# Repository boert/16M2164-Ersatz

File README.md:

# Ersatz für Hybridschaltkreis 16M2164

Der 16M2164 von KWH (Keramische Werke Hermsdorf) ist ein Speicherschaltkreis in Hybridbauweise.
Er ist vermutlich nur in sehr geringen Stückzahlen hergestellt worden.
Der Hybridschaltkreis enthält 16 mal das Die (ein Stück vom Halbleiterwafer) des Schaltkreises U2164 sowie einige Stützkondensatoren auf einem Keramiksubstrat.  
Der U2164 ist ein dynamischer RAM mit 64kBit.
In Summe enthält der 16M2164 ein MegaBit bzw. 128 kByte Speicher.

Zum Einsatz kommt der Schaltkreis 16M2164 im Speichermodul M036 für den KC85 aus Mühlhausen [^1].  
Um die unbestückten Leiterplatte, die für dieses Modul im Umlauf sind, nutzen zu können, benötigt man i.d.R. einen Ersatz für den 16M2164.

Von U. Zander stammt die urspüngliche Idee einer Schaltkreisersatzplatine, die nur mit vier dRAM-Schaltkreisen auskommt [^2].
Diese Lösung funktioniert leider nicht perfekt.

> [!Note]
> ### dynamischer Speicher
> Bei dynamischen Speichern wird die Information als Ladung in Kondensatoren abgebildet. Durch Leckströme verliert sich diese Ladung mit der Zeit und muß daher regelmäßig aufgefrischt werden (Refresh). Dies geschiet u.a. beim Aktivieren des /RAS-Signals. Der Hersteller gibt dabei an, in welchem Zeitraum jede ROW-Adresse einmal aktiviert werden muß. Normalerweise wird die angelegte ROW-Adresse vom Speichercontroller entsprechend hochgezählt. Bei einem geschickt adressierten Bildwiederholspeicher könnte man auf den Refresh verzichten, da dort durch regelmäßige Lesezugriffe die Information beim Lesen aufgefrischt wird.

In der folgenden Tabelle sind die Refreshzyklen eingier dRAM-Hersteller aufgeführt:

Hersteller  | Speicher-IC | Speichergröße | Refreshzyklen | Refreshzeit | Gehäuse
----------  | ----------- | ------------: | ------------: | ----------: | -------
&nbsp;      | &nbsp;      | _x1 Bit dRAMs_ 
Mostek      | MK4096      |   4k x 1      |   64          |  2 ms       | DIP16
Mostek      | MK4116      |  16k x 1      |  128          |  2 ms       | DIP16
NEC         | µPD4164     |  64k x 1      |  128          |  2 ms       | DIP16
Mostek      | MK4564      |  64k x 1      |  128          |  2 ms       | DIP16, PLCC18
Mostek      | MK4164      |  64k x 1      |  128          |  2 ms       | DIP16
National    | NMC4164     |  64k x 1      |  256          |  4 ms       | DIP16
Siemens     | HYB4164     |  64k x 1      |  256          |  4 ms       | DIP16
Mostek      | MK41256     | 256k x 1      |  256          |  4 ms       | DIP16, PLCC18
Siemens     | HYB51100    |   1M x 1      |  512          |  8 ms       | SOJ26
&nbsp;      | &nbsp;      | _x4 Bit dRAMs_ 
TI          | TMS4416     |  16k x 4      |  256          |  4 ms       | DIP18, PLCC18
TI          | SMJ4464     |  64k x 4      |  256          |  4 ms       | DIP18, PLCC18
NEC         | µPD41464    |  64k x 4      |  256          |  4 ms       | DIP18, PLCC18
TI          | SMJ4464     |  64k x 4      |  256          |  4 ms       | DIP18, PLCC18
Mitsubishi  | M5M4464A    |  64k x 4      |  256          |  4 ms       | DIP18, PLCC18, ZIP20
Samsung     | KM41464A    |  64k x 4      |  256          |  4 ms       | DIP18, PLCC18, ZIP20
Siemens     | HYB514256   | 256k x 4      |  512          |  8 ms       | DIP20, SOJ26/20
NEC         | µPD424400   |   1M x 4      | 1024          | 16 ms       | TSOP26, SOJ26/20

Eine Vergleichstabelle von 64k-Bit dRAM-Chips findet sich unter [^7].

Die verwendeten Speicher-IC der Größe 64k x 4 Bit benötigen alle 256 Refreshzyklen. Damit muß der Zähler für den Refresh mindestens acht Bit breit sein.
Die U880/Z80-CPU enthält nur einen 7 Bit-Refreshzähler, der für die Bausteine mit 64 oder 128 Refreshzyklen ausreichend ist.
Die obere Hälfte des Speichers erhält keinen definierten Refresh und verliert mit der Zeit ihren Inhalt.

Im Folgenden sind drei Wege aufgezeigt, um den fehlenden Speicher zu ersetzen: Variante R, Variante D und Variante S.

## Variante R: Refresh
Der übliche Weg ist es, den Refreshzähler zu erweitern.  
Ein Schaltung dafür findet sich z.B. in [^3].

Auch im Grundgerät D001 (KC85/4) werden aus den Signalen /rfsh, mreq und ab6 die Signale RF7 und RF8 gebildet, die den Refreshzähler des Z80 auf 9 Bit erweitern:

Der erweiterte Refreshzähler steht leider nur den interne RAM-Bausteinen auf der Hauptplatine zur Verfügung.

Am Modul 16M2164 steht weder der erweiterte Refreshzähler, noch das eigentliche Refresh-Signal zur Verfügung.  
Zumindest des Refresh-Signal müsste auf separatem Weg zugeführt werden.  
Daher wurde diese Lösung nicht weiter verfolgt.

## Variante D: dynamischer RAM
Im Robotrontechnik-Forum ist ein Bild vom Innenaufbau des 16M2164 verlinkt [^4]. Mit etwas Geschick lassen sich die 16 Stück U2164 auf einer Aufsteckplatine plazieren und so die Schaltung des 16M2164 1:1 nachbilden.
Die erste Hälfte der Schaltkreise sitzt direkt auf der Adapterplatine. Die zweite Hälfte wird huckepack auf die bereits eingelöteten Schaltkreise gelötet und bis auf das /CAS-Signal parallel geschaltet.
Die die untere Hälfte wird mit dem Signal /CAS0 aktiv. Die obere Hälfte wird entsprechend mit dem /CAS1-Signal aktiv.

Der große Nachteil dieser Lösung: sie benötigt zuviel Platz und passt nicht mehr in ein Modulgehäuse bzw. den Modulschacht.
Das M036 läßt sich so nur offen an einem Adapter M007 betreiben.

## Variante S: statischer RAM
Warum ersetzen wir nicht die dRAM-Schaltkreise durch einen einzelnen SRAM der Größe 128kx8 Bit?
Ein SRAM benötigt die Signale /CS, /WE und /OE sowie Daten und Adressen.
Am Bestückungsplatz für das 16M2164 stehen die Signale /RAS, /CAS0 (unter Hälfte), /CAS1 (obere Hälfte) und /WE zur Verfügung. Die Adressenleitungen sind multiplext.

Die Adressen müssen wieder demultiplext werden und für die Steuersignale ist eine Signalanpassung nötig.
Ein Latch, was mit dem invertierten /RAS-Signal angesteuert wird, speichert die eine Hälfte der Adressinformation. Die andere Hälfte der Adresse wird direkt an den SRAM durchgereicht. Aus /CAS0 und /CAS1 wird das /CS-Signal gebildet. Aus dem Signal /WE wird noch das Signal /OE abgeleitet.

Da es ein RAM ist, dürfen Datenleitungen problemlos miteinander vertauscht werden. Ebenso kann man Adressleitungen tauschen, solange keine Sonderfunktionen realisiert sind.
Damit wird das Routing auf der zweilagigen Platine erleichtert.

Im Bild ist die Lösung zu sehen, die von der Grundfläche dem Original 16M2164 entspricht.

Mit flachen Präzisions-Stiftleisten (und ohne IC-Sockel für den SRAM-Chip) läßt sich die Ersatzplatine im Modulgehäuse unterbringen.
Der IC-Sockel im Bild diente für den Test verschiedener SRAM-Schaltkreise.

# Test im M036 #
Für einen Speichertest im KC85/4 bzw. KC85/5 bietet sich das Programm RAMTEST3 an.
Um gezielt nur das Speichermodul M036 zu testen kann man mit `TESTM` den Modulschacht mit angeben, z.B. `TESTM 0C`.
Anschließend werden die acht Segmente des M036 durchgetestet:

# Nutzung des Modul M036 #
## Typestar + RAMDOS ##

Das Textverarbeitungssystemm Typestar[^5] bringt das RAMDOS-System mit. Damit wird das KC-CAOS um eine RAM-Disk erweitert.

## RAM-Disk für MicroDOS (D004) ##

Beim Start von MicroDOS [^6] werden vorhande RAM-Module als RAM-Disk (Laufwerk A:) initialisiert.
Das funktioniert auch mit dem Modul M036:

### Referenzen und Links
[^1]: Modul M036, Beschreibung, Bilder und Handbuch: [Modulbeschreibung auf mpm-kc85.de](http://www.mpm-kc85.de/html/m036_segram128k.htm)

[^2]: Schaltkreisersatzplatine 16M2164 [https://www.sax.de/~zander/ --> Hobby --> KC85 --> Hardware --> 128K-Segmented-RAM-Modul (M036)](https://www.sax.de/~zander/)

[^3]: c't 1984, Heft 9, M. Hungershausen, 8-Bit-Refresh für Z80

[^4]: Bild vom Innenleben des 16M2164 [Forum robotrontechnik.de](https://www.robotrontechnik.de/html/forum/thwb/showtopic.php?threadid=2115)

[^5]: Modul M033, Typestar: [Modulbeschreibung auf mpm-kc85.de](http://www.mpm-kc85.de/html/m033_typestar.htm)

[^6]: MicroDOS:  [Beschreibung auf mpm-kc85.de](http://www.mpm-kc85.de/html/MicroDOS.htm)

[^7]: Vergleichstabelle 64 kBit dRAM-Chips: [Examples of 4164 class RAM chips](https://www.minuszerodegrees.net/memory/4164.htm)

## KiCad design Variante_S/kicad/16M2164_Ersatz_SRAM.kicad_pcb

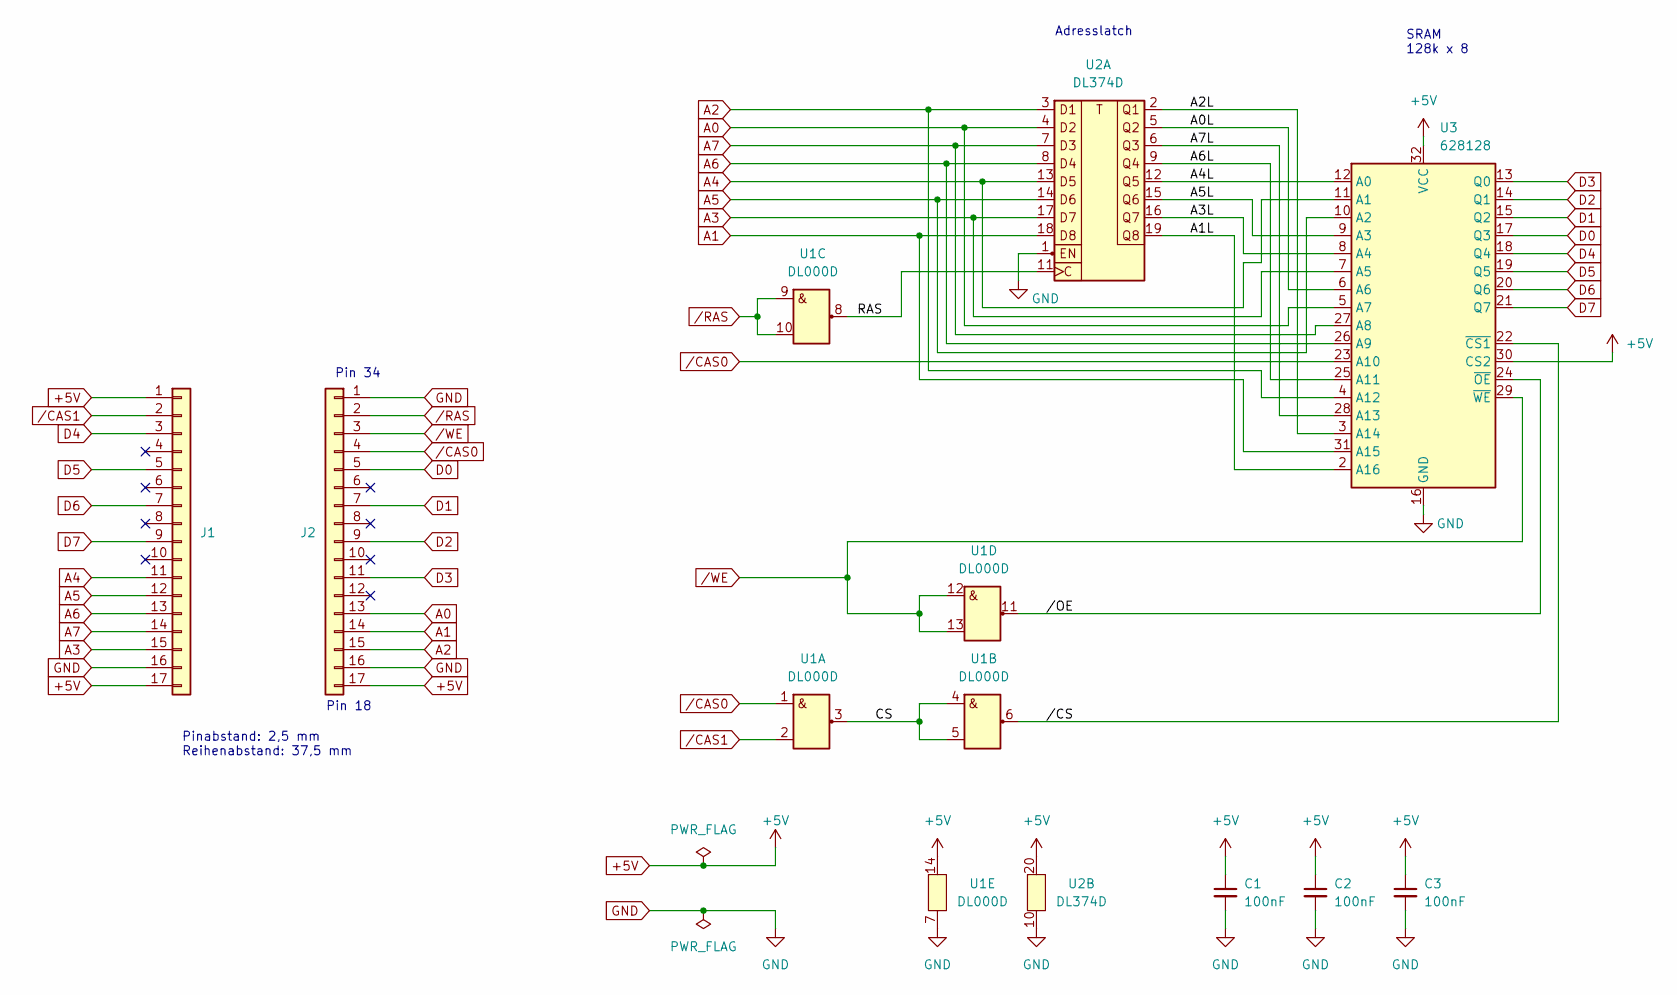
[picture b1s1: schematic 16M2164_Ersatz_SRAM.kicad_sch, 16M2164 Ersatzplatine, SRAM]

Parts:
C1, C2, C3: 100nF; C_1206_3216Metric_Pad1.33x1.80mm_HandSolder
J1, J2: Conn_01x17; PinHeader_1x17_P2.54mm_Vertical
U1: DL000D; DIP-14_W7.62mm_LongPads
U2: DL374D; DIP-20_W7.62mm_LongPads
U3: 628128; DIP-32_W15.24mm_Socket_LongPads

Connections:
+5V: C1.1, C2.1, C3.1, J1.1, J1.17, J2.17, U1.14 (Vcc), U2.20 (Vcc), U3.30 (CS2), U3.32 (VCC)
/A0L: U2.5 (Q2), U3.6 (A6)
/A1L: U2.19 (Q8), U3.2 (A16)
/A2L: U2.2 (Q1), U3.3 (A14)
/A3L: U2.16 (Q7), U3.8 (A4)
/A4L: U2.12 (Q5), U3.12 (A0)
/A5L: U2.15 (Q6), U3.9 (A3)
/A6L: U2.9 (Q4), U3.25 (A11)
/A7L: U2.6 (Q3), U3.28 (A13)
/CS: U1.3 (Y1), U1.4 (A2), U1.5 (B2)
/RAS: U1.8 (Y3), U2.11 (C)
//CS: U1.6 (Y2), U3.22 (~CS1)
//OE: U1.11 (Y4), U3.24 (~OE)
A0: J2.13, U2.4 (D2), U3.5 (A7)
A1: J2.14, U2.18 (D8), U3.31 (A15)
A2: J2.15, U2.3 (D1), U3.4 (A12)
A3: J1.15, U2.17 (D7), U3.7 (A5)
A4: J1.11, U2.13 (D5), U3.11 (A1)
A5: J1.12, U2.14 (D6), U3.10 (A2)
A6: J1.13, U2.8 (D4), U3.26 (A9)
A7: J1.14, U2.7 (D3), U3.27 (A8)
D0: J2.5, U3.17 (Q3)
D1: J2.7, U3.15 (Q2)
D2: J2.9, U3.14 (Q1)
D3: J2.11, U3.13 (Q0)
D4: J1.3, U3.18 (Q4)
D5: J1.5, U3.19 (Q5)
D6: J1.7, U3.20 (Q6)
D7: J1.9, U3.21 (Q7)
GND: C1.2, C2.2, C3.2, J1.16, J2.1, J2.16, U1.7 (GND), U2.1 (EN), U2.10 (GND), U3.16 (GND)
/CAS0: J2.4, U1.1 (A1), U3.23 (A10)
/CAS1: J1.2, U1.2 (B1)
/RAS: J2.2, U1.9 (A3), U1.10 (B3)
/WE: J2.3, U1.12 (A4), U1.13 (B4), U3.29 (~WE)

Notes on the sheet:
Adresslatch
Pin 34
SRAM 128k x 8
Pin 18
Pinabstand: 2,5 mm Reihenabstand: 37,5 mm

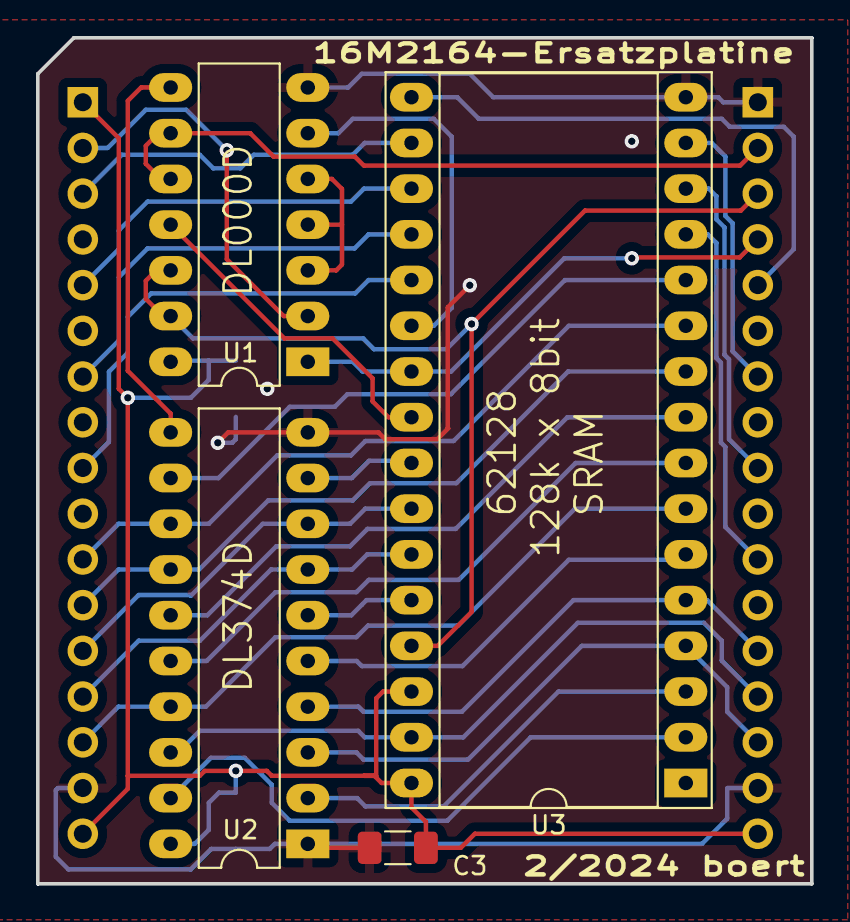
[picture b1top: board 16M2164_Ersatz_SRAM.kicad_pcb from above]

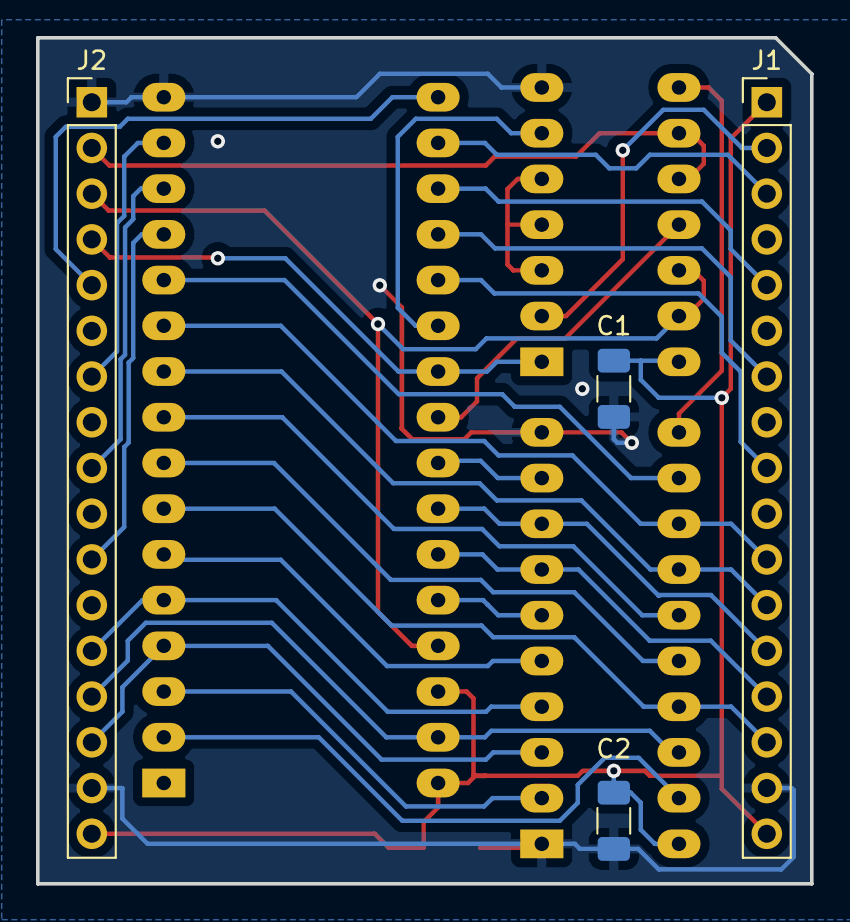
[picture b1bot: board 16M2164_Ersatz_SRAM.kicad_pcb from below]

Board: 2 copper layers, 43.0 x 47.0 mm, 8 parts (4 on the bottom side), 34 nets.

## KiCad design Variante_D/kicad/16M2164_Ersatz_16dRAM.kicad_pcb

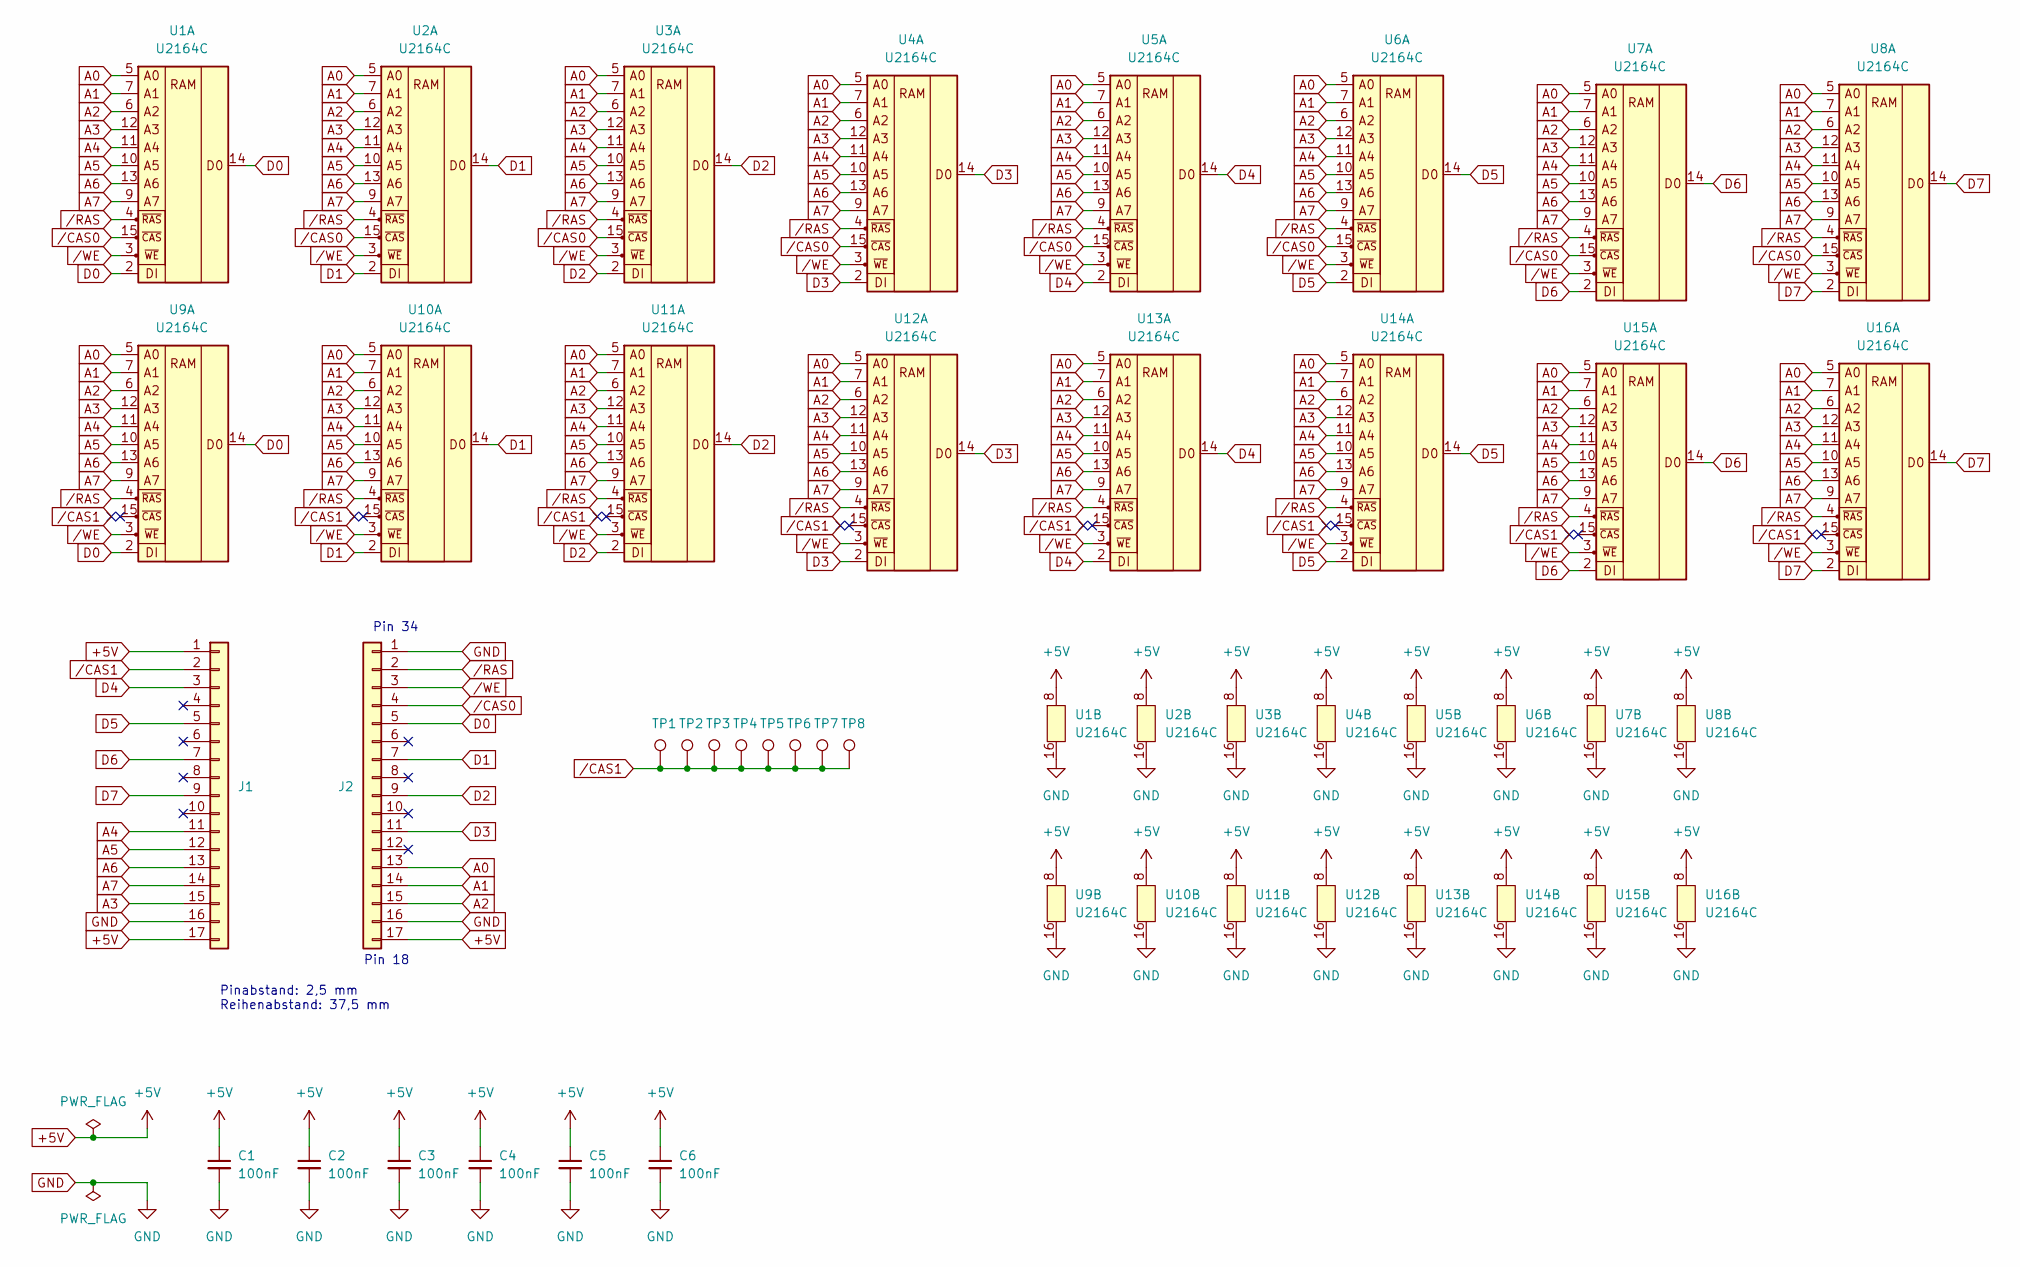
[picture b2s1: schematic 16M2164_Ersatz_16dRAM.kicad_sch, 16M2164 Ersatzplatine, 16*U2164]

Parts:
C1, C2, C3, C4, C5, C6: 100nF; C_1206_3216Metric_Pad1.33x1.80mm_HandSolder
J1, J2: Conn_01x17; PinHeader_1x17_P2.54mm_Vertical
TP1, TP2, TP3, TP4, TP5, TP6, TP7, TP8: TestPoint; TestPoint_Loop_D1.80mm_Drill1.0mm_Beaded
U1, U2, U3, U4, U5, U6, U7, U8, U9, U10, U11, U12, U13, U14, U15, U16: U2164C; DIP-16_W7.62mm_LongPads

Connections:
+5V: C1.1, C2.1, C3.1, C4.1, C5.1, C6.1, J1.1, J1.17, J2.17, U1.8 (Ucc), U2.8 (Ucc), U3.8 (Ucc), U4.8 (Ucc), U5.8 (Ucc), U6.8 (Ucc), U7.8 (Ucc), U8.8 (Ucc), U9.8 (Ucc), U10.8 (Ucc), U11.8 (Ucc), U12.8 (Ucc), U13.8 (Ucc), U14.8 (Ucc), U15.8 (Ucc), U16.8 (Ucc)
A0: J2.13, U1.5 (A0), U2.5 (A0), U3.5 (A0), U4.5 (A0), U5.5 (A0), U6.5 (A0), U7.5 (A0), U8.5 (A0), U9.5 (A0), U10.5 (A0), U11.5 (A0), U12.5 (A0), U13.5 (A0), U14.5 (A0), U15.5 (A0), U16.5 (A0)
A1: J2.14, U1.7 (A1), U2.7 (A1), U3.7 (A1), U4.7 (A1), U5.7 (A1), U6.7 (A1), U7.7 (A1), U8.7 (A1), U9.7 (A1), U10.7 (A1), U11.7 (A1), U12.7 (A1), U13.7 (A1), U14.7 (A1), U15.7 (A1), U16.7 (A1)
A2: J2.15, U1.6 (A2), U2.6 (A2), U3.6 (A2), U4.6 (A2), U5.6 (A2), U6.6 (A2), U7.6 (A2), U8.6 (A2), U9.6 (A2), U10.6 (A2), U11.6 (A2), U12.6 (A2), U13.6 (A2), U14.6 (A2), U15.6 (A2), U16.6 (A2)
A3: J1.15, U1.12 (A3), U2.12 (A3), U3.12 (A3), U4.12 (A3), U5.12 (A3), U6.12 (A3), U7.12 (A3), U8.12 (A3), U9.12 (A3), U10.12 (A3), U11.12 (A3), U12.12 (A3), U13.12 (A3), U14.12 (A3), U15.12 (A3), U16.12 (A3)
A4: J1.11, U1.11 (A4), U2.11 (A4), U3.11 (A4), U4.11 (A4), U5.11 (A4), U6.11 (A4), U7.11 (A4), U8.11 (A4), U9.11 (A4), U10.11 (A4), U11.11 (A4), U12.11 (A4), U13.11 (A4), U14.11 (A4), U15.11 (A4), U16.11 (A4)
A5: J1.12, U1.10 (A5), U2.10 (A5), U3.10 (A5), U4.10 (A5), U5.10 (A5), U6.10 (A5), U7.10 (A5), U8.10 (A5), U9.10 (A5), U10.10 (A5), U11.10 (A5), U12.10 (A5), U13.10 (A5), U14.10 (A5), U15.10 (A5), U16.10 (A5)
A6: J1.13, U1.13 (A6), U2.13 (A6), U3.13 (A6), U4.13 (A6), U5.13 (A6), U6.13 (A6), U7.13 (A6), U8.13 (A6), U9.13 (A6), U10.13 (A6), U11.13 (A6), U12.13 (A6), U13.13 (A6), U14.13 (A6), U15.13 (A6), U16.13 (A6)
A7: J1.14, U1.9 (A7), U2.9 (A7), U3.9 (A7), U4.9 (A7), U5.9 (A7), U6.9 (A7), U7.9 (A7), U8.9 (A7), U9.9 (A7), U10.9 (A7), U11.9 (A7), U12.9 (A7), U13.9 (A7), U14.9 (A7), U15.9 (A7), U16.9 (A7)
D0: J2.5, U1.2 (DI), U1.14 (D0), U9.2 (DI), U9.14 (D0)
D1: J2.7, U2.2 (DI), U2.14 (D0), U10.2 (DI), U10.14 (D0)
D2: J2.9, U3.2 (DI), U3.14 (D0), U11.2 (DI), U11.14 (D0)
D3: J2.11, U4.2 (DI), U4.14 (D0), U12.2 (DI), U12.14 (D0)
D4: J1.3, U5.2 (DI), U5.14 (D0), U13.2 (DI), U13.14 (D0)
D5: J1.5, U6.2 (DI), U6.14 (D0), U14.2 (DI), U14.14 (D0)
D6: J1.7, U7.2 (DI), U7.14 (D0), U15.2 (DI), U15.14 (D0)
D7: J1.9, U8.2 (DI), U8.14 (D0), U16.2 (DI), U16.14 (D0)
GND: C1.2, C2.2, C3.2, C4.2, C5.2, C6.2, J1.16, J2.1, J2.16, U1.16 (Uss), U2.16 (Uss), U3.16 (Uss), U4.16 (Uss), U5.16 (Uss), U6.16 (Uss), U7.16 (Uss), U8.16 (Uss), U9.16 (Uss), U10.16 (Uss), U11.16 (Uss), U12.16 (Uss), U13.16 (Uss), U14.16 (Uss), U15.16 (Uss), U16.16 (Uss)
/CAS0: J2.4, U1.15 (~CAS), U2.15 (~CAS), U3.15 (~CAS), U4.15 (~CAS), U5.15 (~CAS), U6.15 (~CAS), U7.15 (~CAS), U8.15 (~CAS)
/CAS1: J1.2, TP1.1, TP2.1, TP3.1, TP4.1, TP5.1, TP6.1, TP7.1, TP8.1
/RAS: J2.2, U1.4 (~RAS), U2.4 (~RAS), U3.4 (~RAS), U4.4 (~RAS), U5.4 (~RAS), U6.4 (~RAS), U7.4 (~RAS), U8.4 (~RAS), U9.4 (~RAS), U10.4 (~RAS), U11.4 (~RAS), U12.4 (~RAS), U13.4 (~RAS), U14.4 (~RAS), U15.4 (~RAS), U16.4 (~RAS)
/WE: J2.3, U1.3 (~WE), U2.3 (~WE), U3.3 (~WE), U4.3 (~WE), U5.3 (~WE), U6.3 (~WE), U7.3 (~WE), U8.3 (~WE), U9.3 (~WE), U10.3 (~WE), U11.3 (~WE), U12.3 (~WE), U13.3 (~WE), U14.3 (~WE), U15.3 (~WE), U16.3 (~WE)

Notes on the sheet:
Pin 34
Pin 18
Pinabstand: 2,5 mm Reihenabstand: 37,5 mm

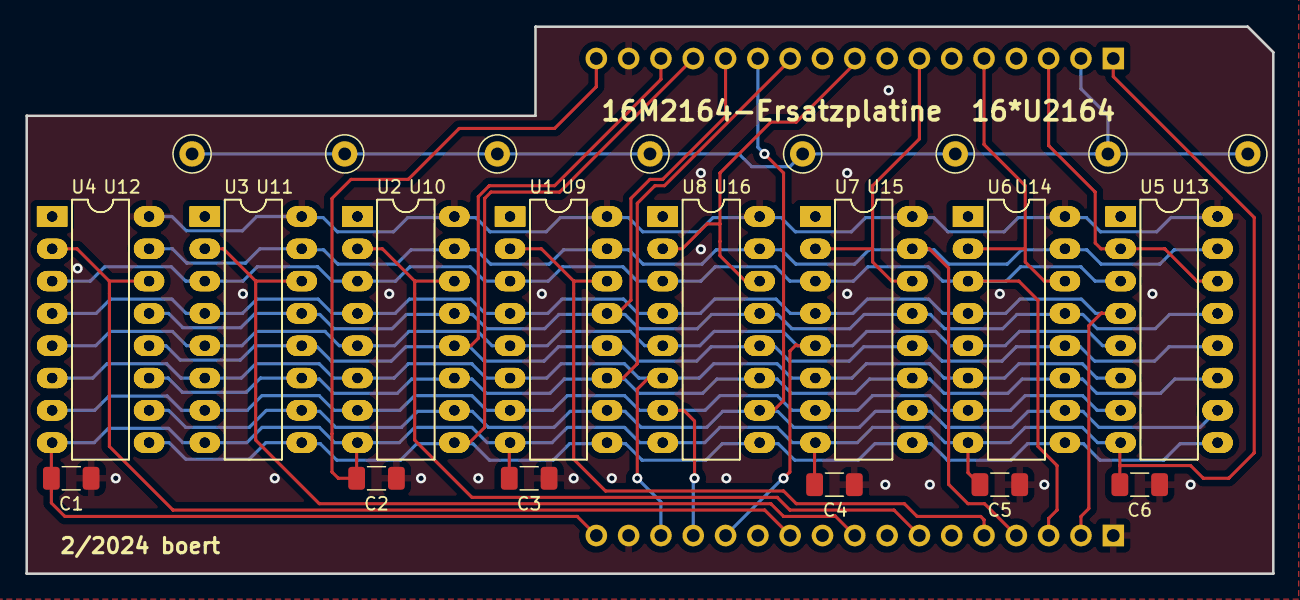
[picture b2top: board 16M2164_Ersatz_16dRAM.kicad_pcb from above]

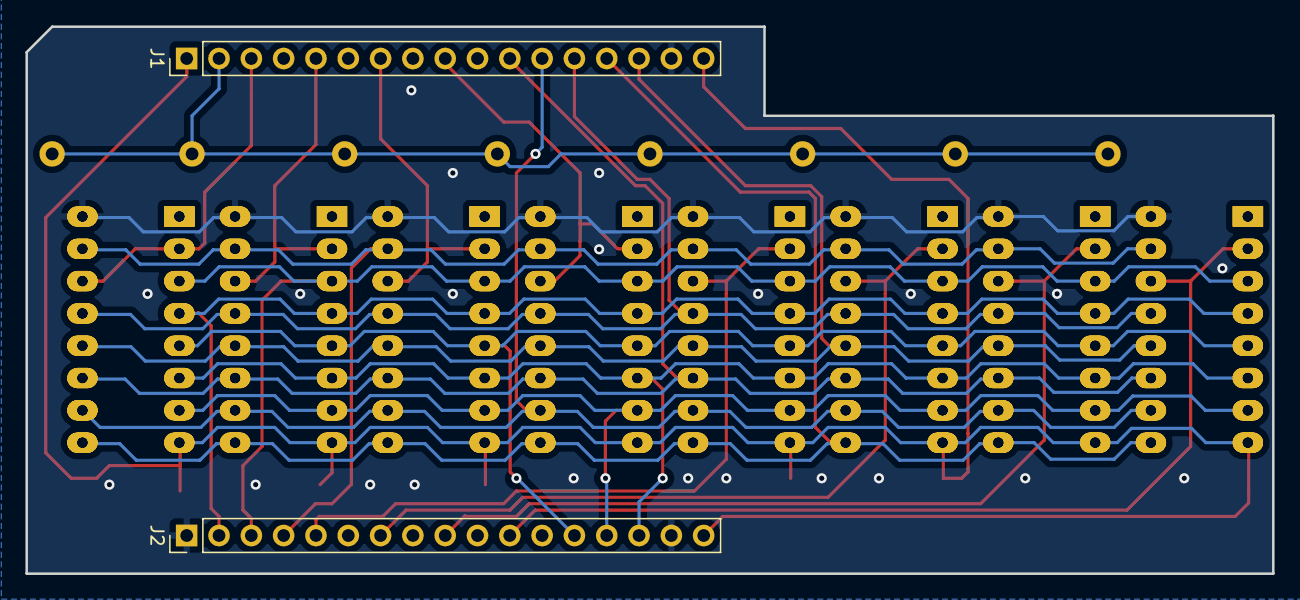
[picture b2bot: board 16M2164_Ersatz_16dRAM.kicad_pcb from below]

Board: 2 copper layers, 98.0 x 43.0 mm, 32 parts (2 on the bottom side), 22 nets.

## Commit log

2024-02-26 first try
2024-02-28 upate pictures
2024-02-29 add: picture
2024-02-29 add: pictures
2024-02-29 add: Variante R
2024-02-29 add: Variante D
2024-02-29 add: Variante S
2024-03-10 add: Refresh-Test
2024-03-10 update: README
2024-03-25 add: Modulblende
2024-03-28 fix: typo
2025-06-29 change: IC-Sockel + Modulgehäuse präzisiert
2026-05-05 fix: table, add: link
